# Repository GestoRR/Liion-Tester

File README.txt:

v0.x.x - Proof of Concept

For the project, Eagle v9.6.2 software was used.

Creation and implementation of the electrical schematic and PCB design for a Li-ion cell tester.
The tester monitors open-circuit voltage, internal resistance, State of Charge (SoC), Depth of Discharge (DoD), and State of Health (SoH).

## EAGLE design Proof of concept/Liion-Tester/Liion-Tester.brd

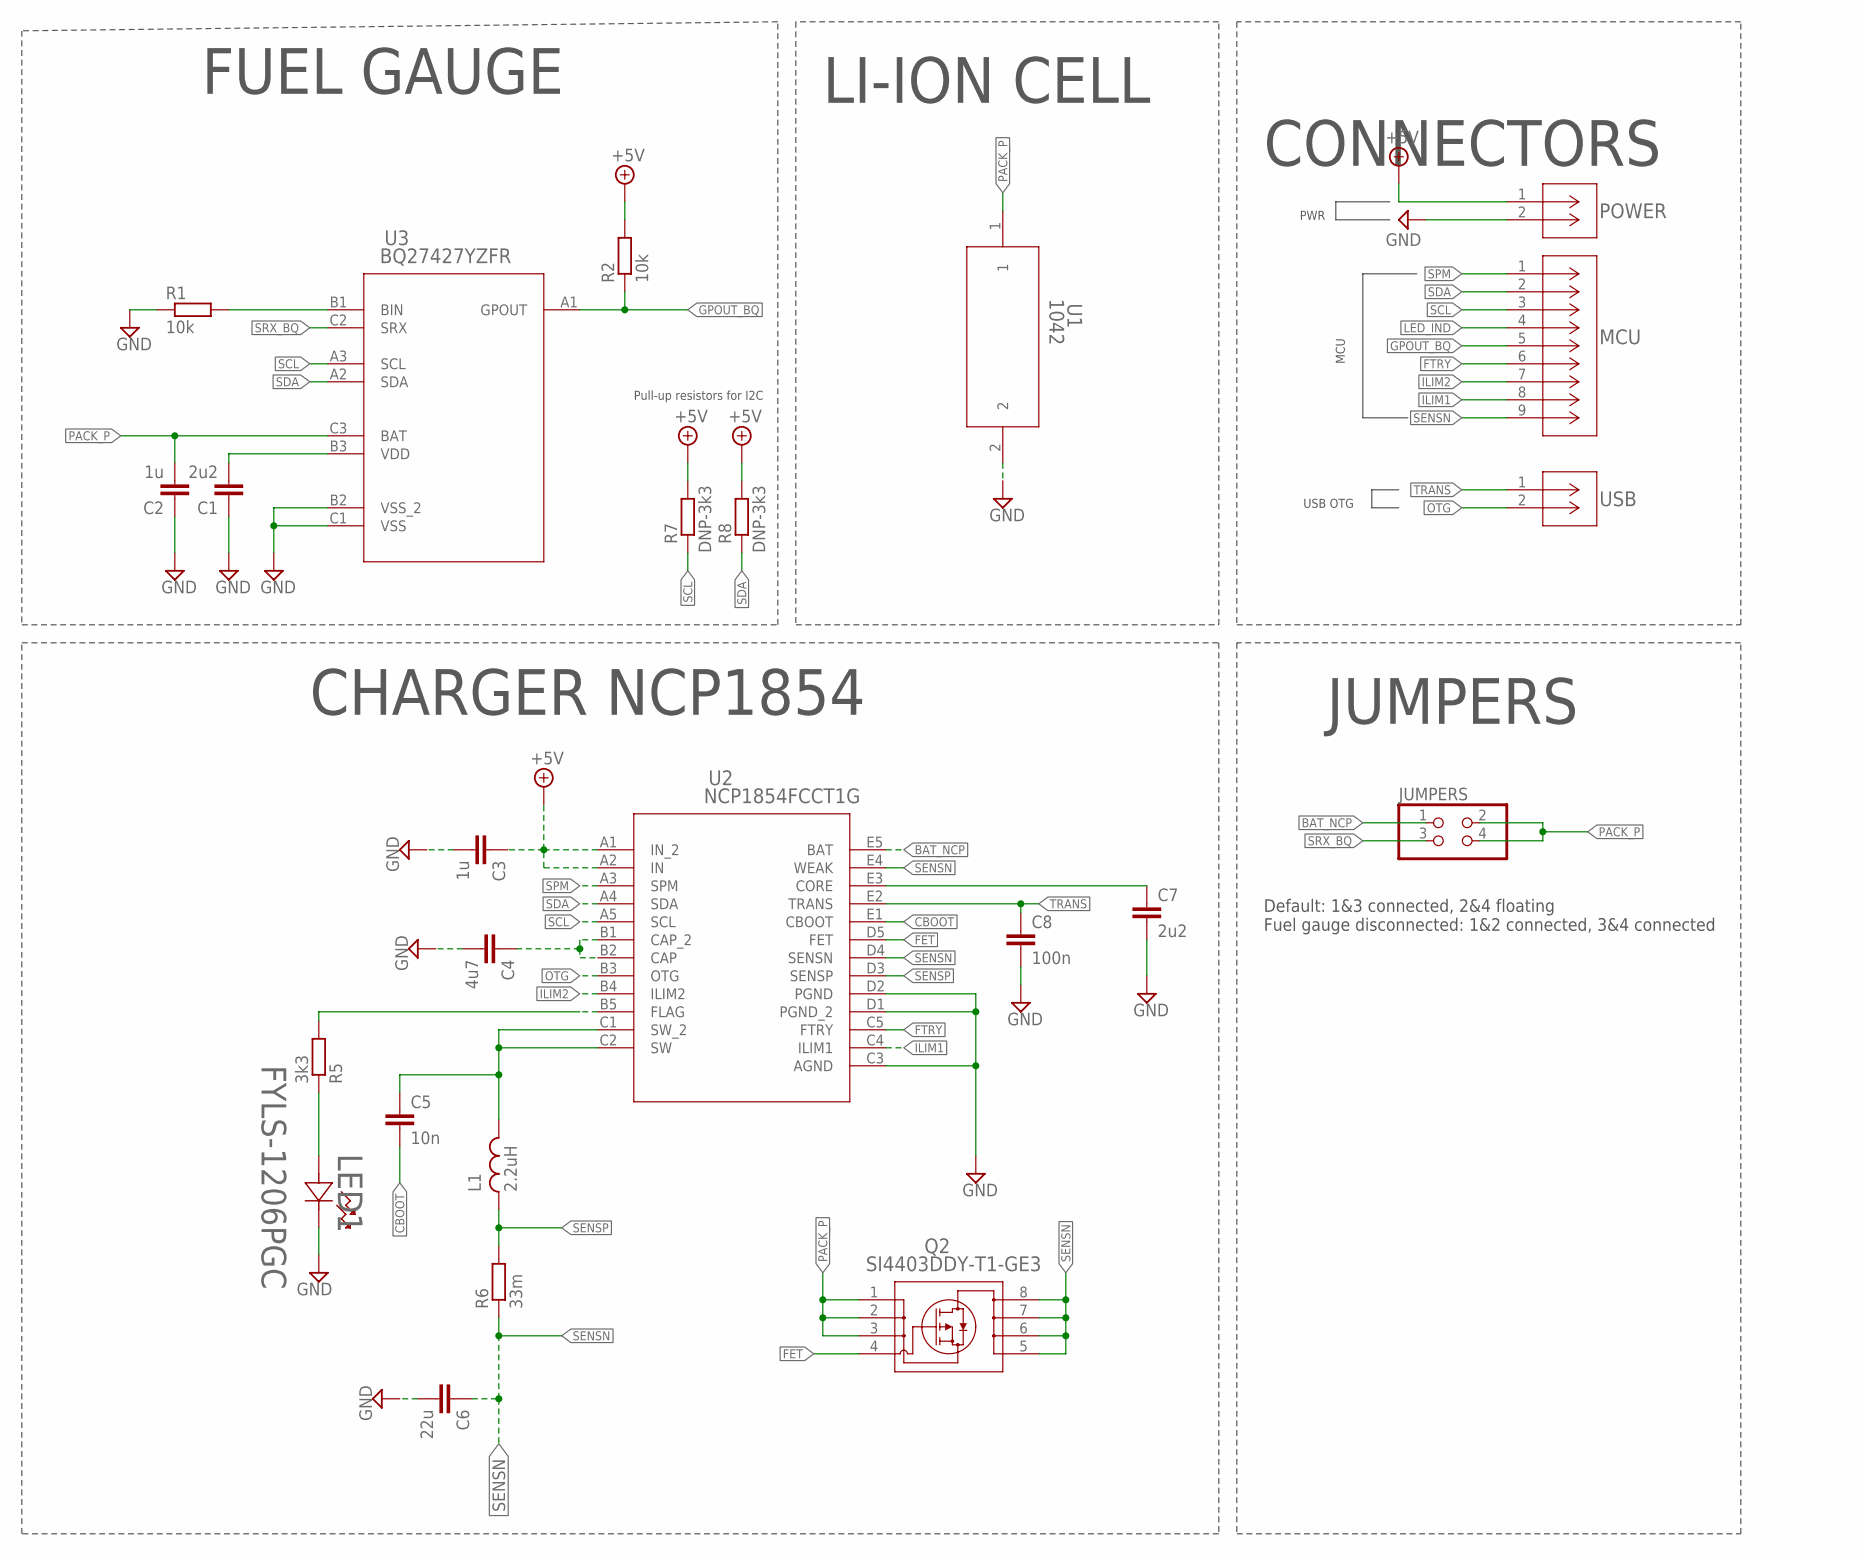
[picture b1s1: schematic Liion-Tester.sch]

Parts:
C1, C7: 2u2; C0603
C2, C3: 1u; C0603
C4: 4u7; C0603
C5: 10n; C0603
C6: 22u; C0603
C8: 100n; C0603
JUMPERS: PINHD-2X2; 2X02
L1: 2.2uH; SPM3012T-2R2M-LR
LED1: FYLS-1206PGC; LED_QBLP650_1206_QTB
MCU: 250-109; CONN_250-109_WAG
POWER: 250-102; CONN_250-102_WAG
Q2: SI4403DDY-T1-GE3; SO-8_MS-012_VIS
R1, R2: 10k; R0603
R5: 3k3; R0603
R6: 33m; R2512
R7, R8: DNP-3k3; R0603
U1: 1042; 1042_KEY
U2: NCP1854FCCT1G; BGA25_2P55X2P2_ONS
U3: BQ27427YZFR; DSBGA9-YZF_TEX
USB: 250-102; CONN_250-102_WAG

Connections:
+5V: C3.1, POWER.1, R2.2, R7.2, R8.2, U2.A1 (IN_2), U2.A2 (IN)
BAT_NCP: JUMPERS.1, U2.E5 (BAT)
CBOOT: C5.2, U2.E1 (CBOOT)
FET: Q2.4, U2.D5 (FET)
FTRY: MCU.6, U2.C5 (FTRY)
GND: C1.1, C2.1, C3.2, C4.2, C6.2, C7.2, C8.2, LED1.1 (CATHODE), POWER.2, R1.1, U1.2, U2.C3 (AGND), U2.D1 (PGND_2), U2.D2 (PGND), U3.B2 (VSS_2), U3.C1 (VSS)
GPOUT_BQ: MCU.5, R2.1, U3.A1 (GPOUT)
ILIM1: MCU.8, U2.C4 (ILIM1)
ILIM2: MCU.7, U2.B4 (ILIM2)
LED_IND: MCU.4, R5.2, U2.B5 (FLAG)
unnamed: C1.2, U3.B3 (VDD)
unnamed: R1.2, U3.B1 (BIN)
unnamed: C4.1, U2.B1 (CAP_2), U2.B2 (CAP)
unnamed: LED1.2 (ANODE), R5.1
unnamed: C5.1, L1.P$2 (2), U2.C1 (SW_2), U2.C2 (SW)
unnamed: C7.1, U2.E3 (CORE)
OTG: U2.B3 (OTG), USB.2
PACK_P: C2.2, JUMPERS.2, JUMPERS.4, Q2.1, Q2.2, Q2.3, U1.1, U3.C3 (BAT)
SCL: MCU.3, R7.1, U2.A5 (SCL), U3.A3 (SCL)
SDA: MCU.2, R8.1, U2.A4 (SDA), U3.A2 (SDA)
SENSN: C6.1, MCU.9, Q2.5, Q2.6, Q2.7, Q2.8, R6.1, U2.D4 (SENSN), U2.E4 (WEAK)
SENSP: L1.P$1 (1), R6.2, U2.D3 (SENSP)
SPM: MCU.1, U2.A3 (SPM)
SRX_BQ: JUMPERS.3, U3.C2 (SRX)
TRANS: C8.1, U2.E2 (TRANS), USB.1

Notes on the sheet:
FUEL GAUGE
LI-ION CELL
CHARGER NCP1854
Pull-up resistors for I2C
CONNECTORS
USB OTG
MCU
PWR
JUMPERS
Default: 1&3 connected, 2&4 floating Fuel gauge disconnected: 1&2 connected, 3&4 connected

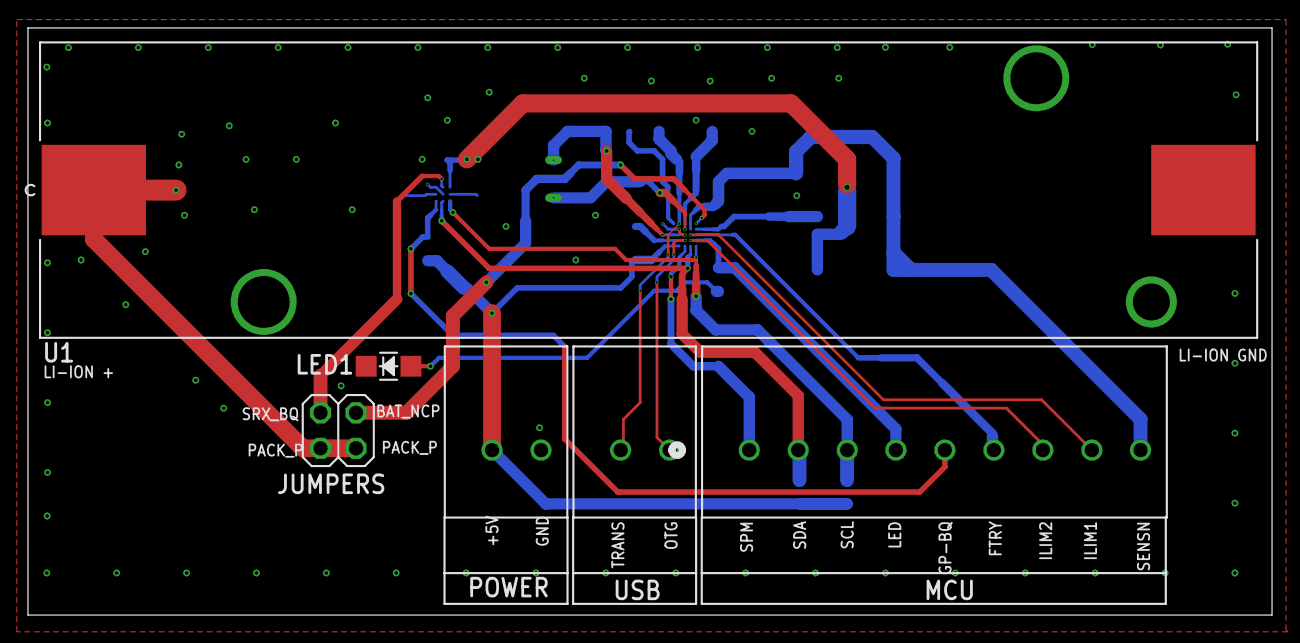
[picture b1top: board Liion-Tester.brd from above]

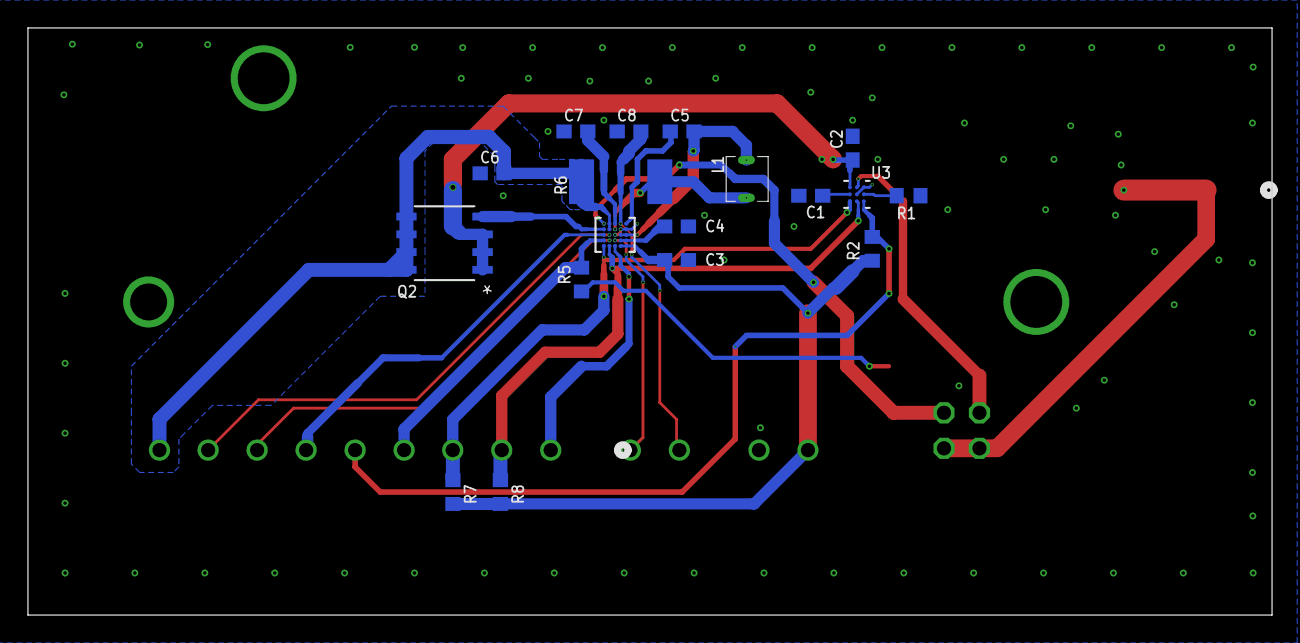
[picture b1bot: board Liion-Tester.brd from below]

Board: 4 copper layers, 89.0 x 42.0 mm, 24 parts (18 on the bottom side), 25 nets.

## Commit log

2024-07-14 NCP1854 finished connections
2024-07-16 Rework of BQ and NCP. Connector added to schematic.
2024-07-22 Final changes in .sch before making .brd
2024-07-25 Version control
2024-07-27 Finished .brd with changes in schematic
2024-08-17 Added polygons for PACK_P and SENS_N
2024-08-19 Eliminated one air wire
2024-08-29 Bigger vias and 4 layer pcb to order from JLCPCB

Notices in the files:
parts and their libraries:
COPYRIGHT: Copyright (C) 2024 Ultra Librarian. All rights reserved.
